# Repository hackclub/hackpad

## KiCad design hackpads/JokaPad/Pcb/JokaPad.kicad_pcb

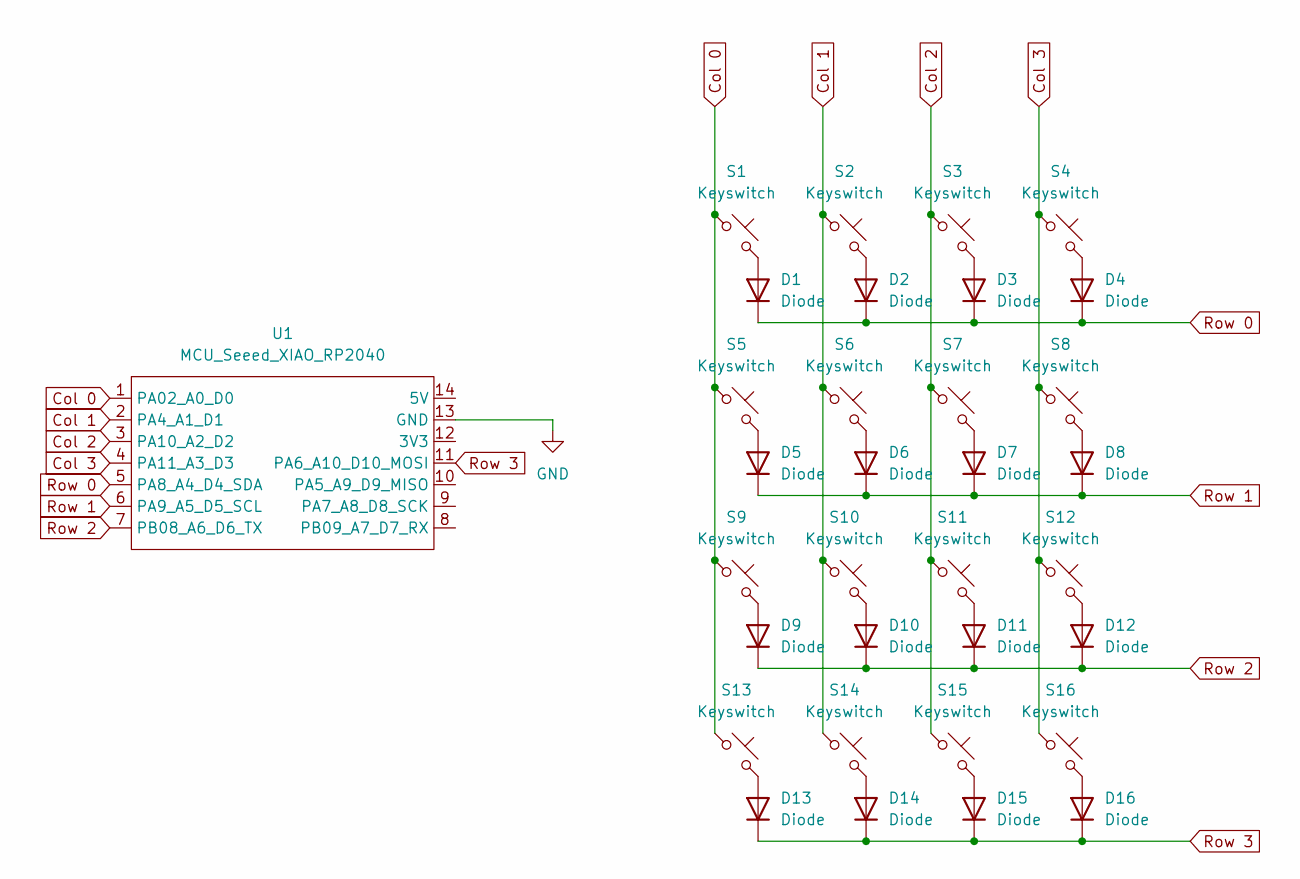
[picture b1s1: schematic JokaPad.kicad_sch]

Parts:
D1, D2, D3, D4, D5, D6, D7, D8, D9, D10, D11, D12, D13, D14, D15, D16: Diode; Diode_DO-35
S1, S2, S3, S4, S5, S6, S7, S8, S9, S10, S11, S12, S13, S14, S15, S16: Keyswitch; MX_PCB_1.00u
U1: MCU_Seeed_XIAO_RP2040; MOUDLE14P-2.54-21X17.8MM

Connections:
Col 0: S1.1, S5.1, S9.1, S13.1, U1.1 (PA02_A0_D0)
Col 1: S2.1, S6.1, S10.1, S14.1, U1.2 (PA4_A1_D1)
Col 2: S3.1, S7.1, S11.1, S15.1, U1.3 (PA10_A2_D2)
Col 3: S4.1, S8.1, S12.1, S16.1, U1.4 (PA11_A3_D3)
GND: U1.13 (GND)
unnamed: D1.2 (A), S1.2
unnamed: D2.2 (A), S2.2
unnamed: D3.2 (A), S3.2
unnamed: D4.2 (A), S4.2
unnamed: D5.2 (A), S5.2
unnamed: D6.2 (A), S6.2
unnamed: D7.2 (A), S7.2
unnamed: D8.2 (A), S8.2
unnamed: D9.2 (A), S9.2
unnamed: D10.2 (A), S10.2
unnamed: D11.2 (A), S11.2
unnamed: D12.2 (A), S12.2
unnamed: D13.2 (A), S13.2
unnamed: D14.2 (A), S14.2
unnamed: D15.2 (A), S15.2
unnamed: D16.2 (A), S16.2
Row 0: D1.1 (K), D2.1 (K), D3.1 (K), D4.1 (K), U1.5 (PA8_A4_D4_SDA)
Row 1: D5.1 (K), D6.1 (K), D7.1 (K), D8.1 (K), U1.6 (PA9_A5_D5_SCL)
Row 2: D9.1 (K), D10.1 (K), D11.1 (K), D12.1 (K), U1.7 (PB08_A6_D6_TX)
Row 3: D13.1 (K), D14.1 (K), D15.1 (K), D16.1 (K), U1.11 (PA6_A10_D10_MOSI)

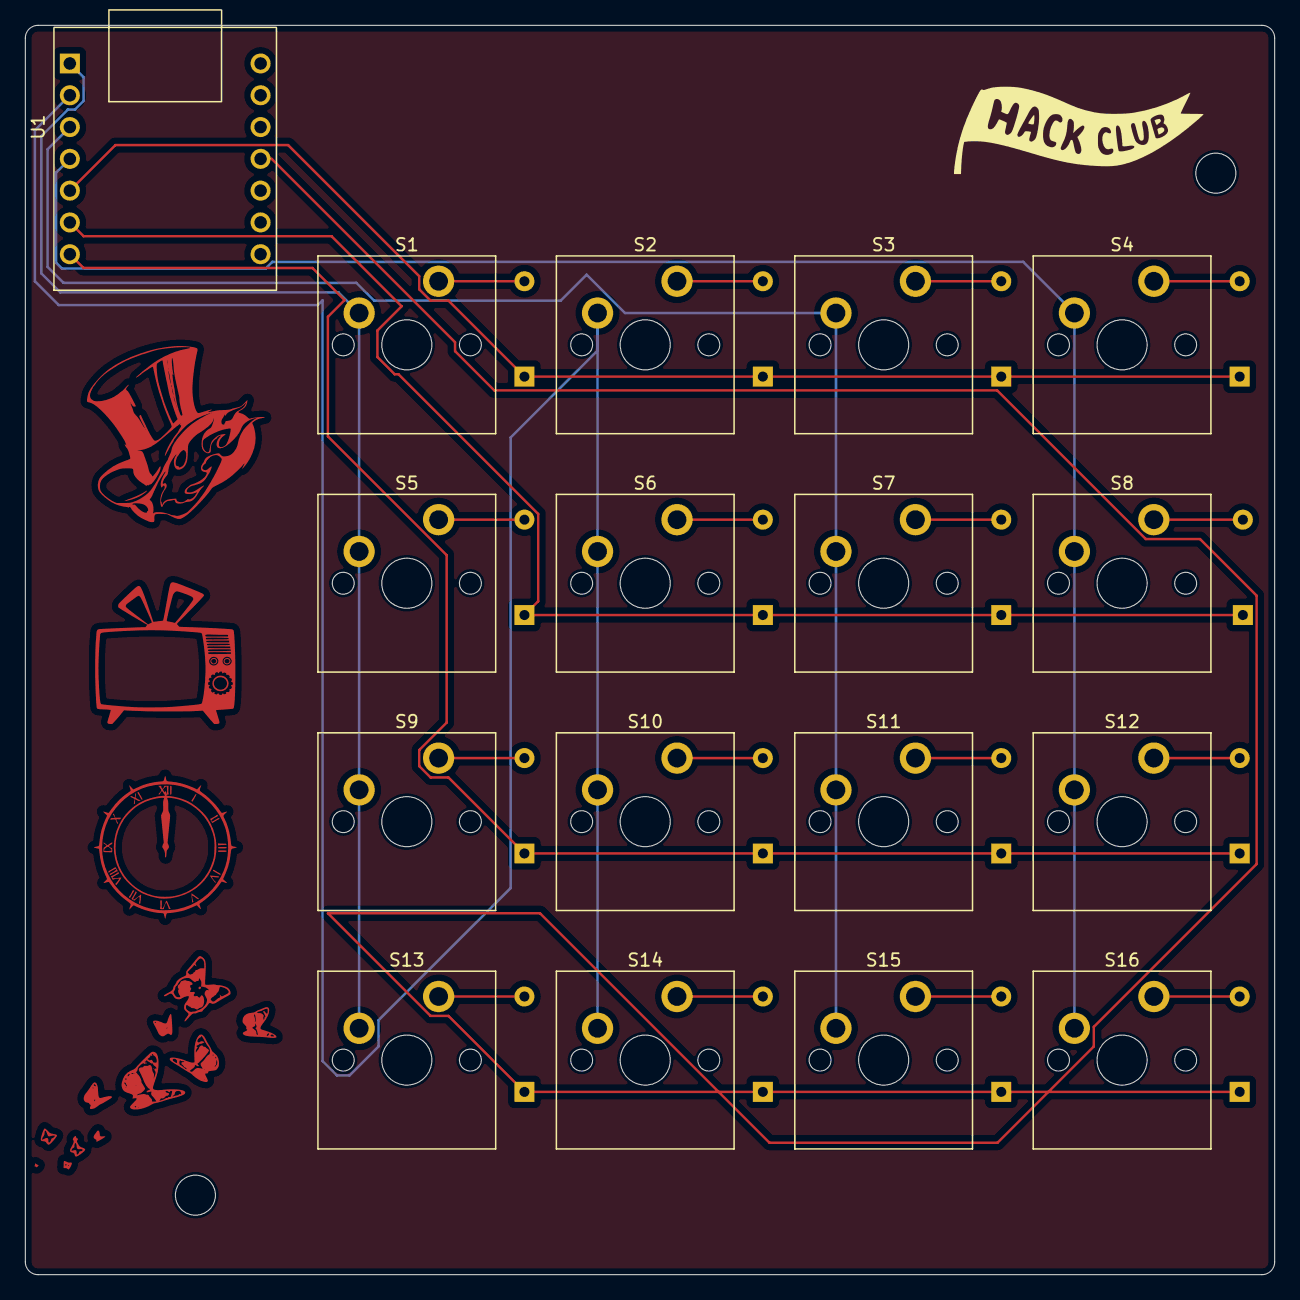
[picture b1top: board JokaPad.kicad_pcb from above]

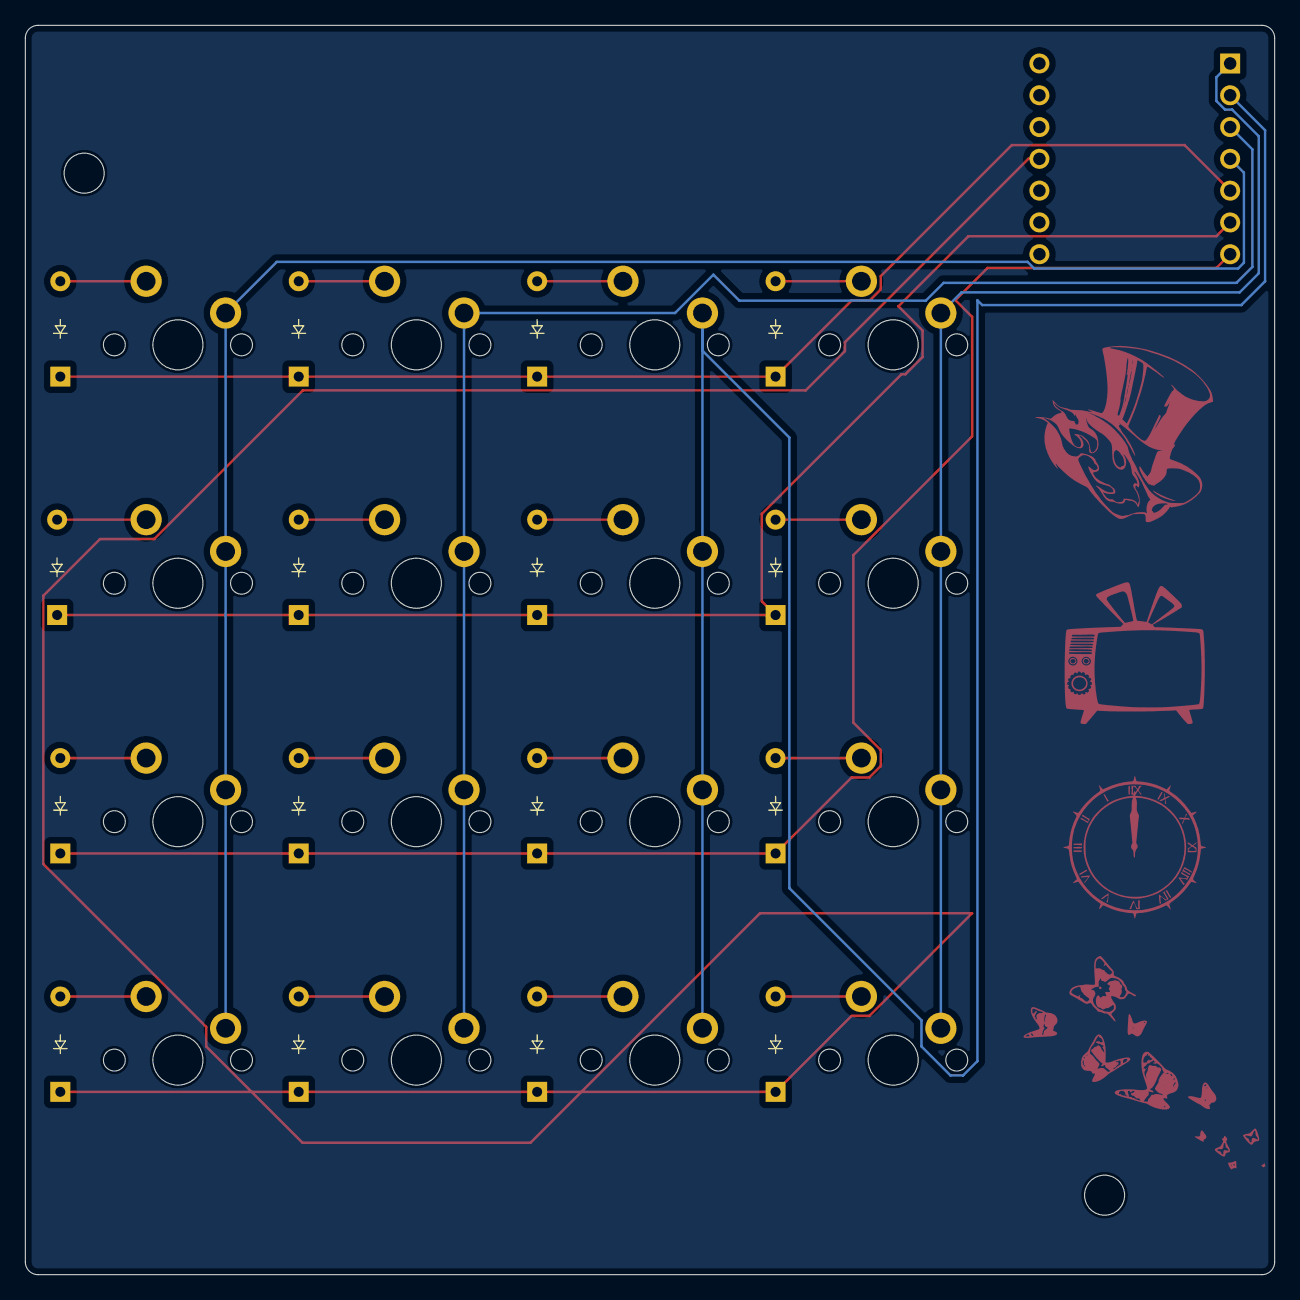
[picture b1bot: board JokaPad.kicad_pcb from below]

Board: 2 copper layers, 99.8 x 99.8 mm, 33 parts (16 on the bottom side), 24 nets.

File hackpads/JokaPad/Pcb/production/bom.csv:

Designator,Footprint,Quantity,Value,LCSC Part #
"D1, D10, D11, D12, D13, D14, D15, D16, D2, D3, D4, D5, D6, D7, D8, D9",Diode_DO-35,16,Diode,
"S1, S10, S11, S12, S13, S14, S15, S16, S2, S3, S4, S5, S6, S7, S8, S9",MX_PCB_1.00u,16,Keyswitch,
U1,MOUDLE14P-2.54-21X17.8MM,1,MCU_Seeed_XIAO_RP2040,

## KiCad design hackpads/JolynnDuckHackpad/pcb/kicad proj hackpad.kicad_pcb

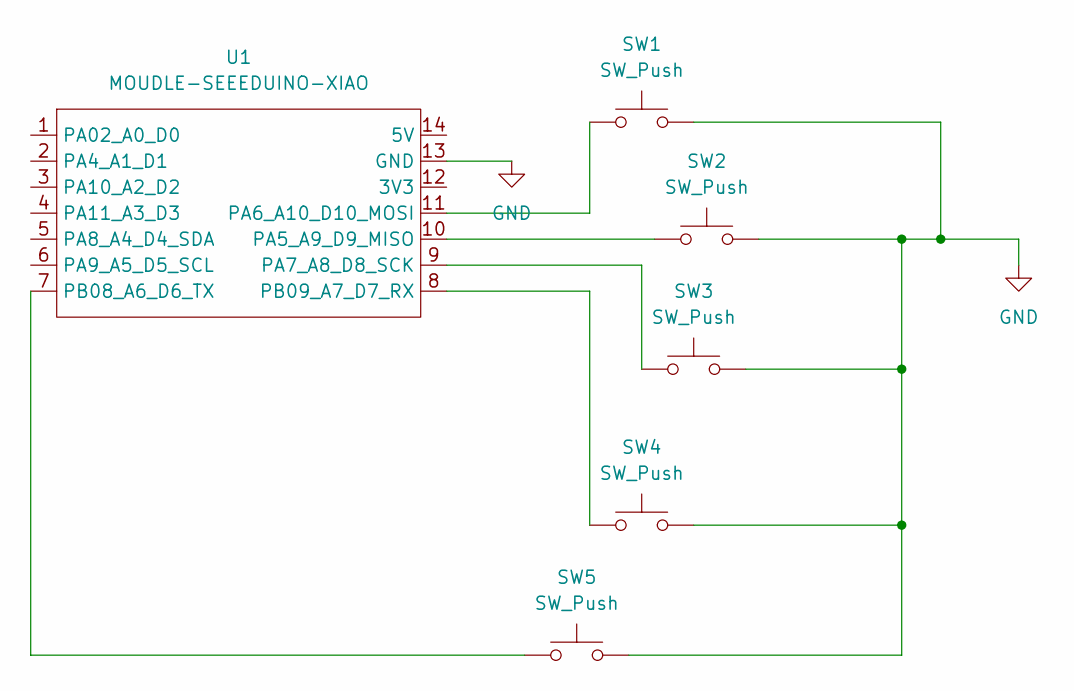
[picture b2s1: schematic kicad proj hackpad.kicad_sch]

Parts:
SW1, SW2, SW3, SW4, SW5: SW_Push; SW_Cherry_MX_1.00u_PCB
U1: MOUDLE-SEEEDUINO-XIAO; XIAO-Generic-Hybrid-14P-2.54-21X17.8MM

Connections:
GND: SW1.2, SW2.2, SW3.2, SW4.2, SW5.2, U1.13 (GND)
unnamed: SW2.1, U1.10 (PA5_A9_D9_MISO)
unnamed: SW1.1, U1.11 (PA6_A10_D10_MOSI)
unnamed: SW3.1, U1.9 (PA7_A8_D8_SCK)
unnamed: SW5.1, U1.7 (PB08_A6_D6_TX)
unnamed: SW4.1, U1.8 (PB09_A7_D7_RX)

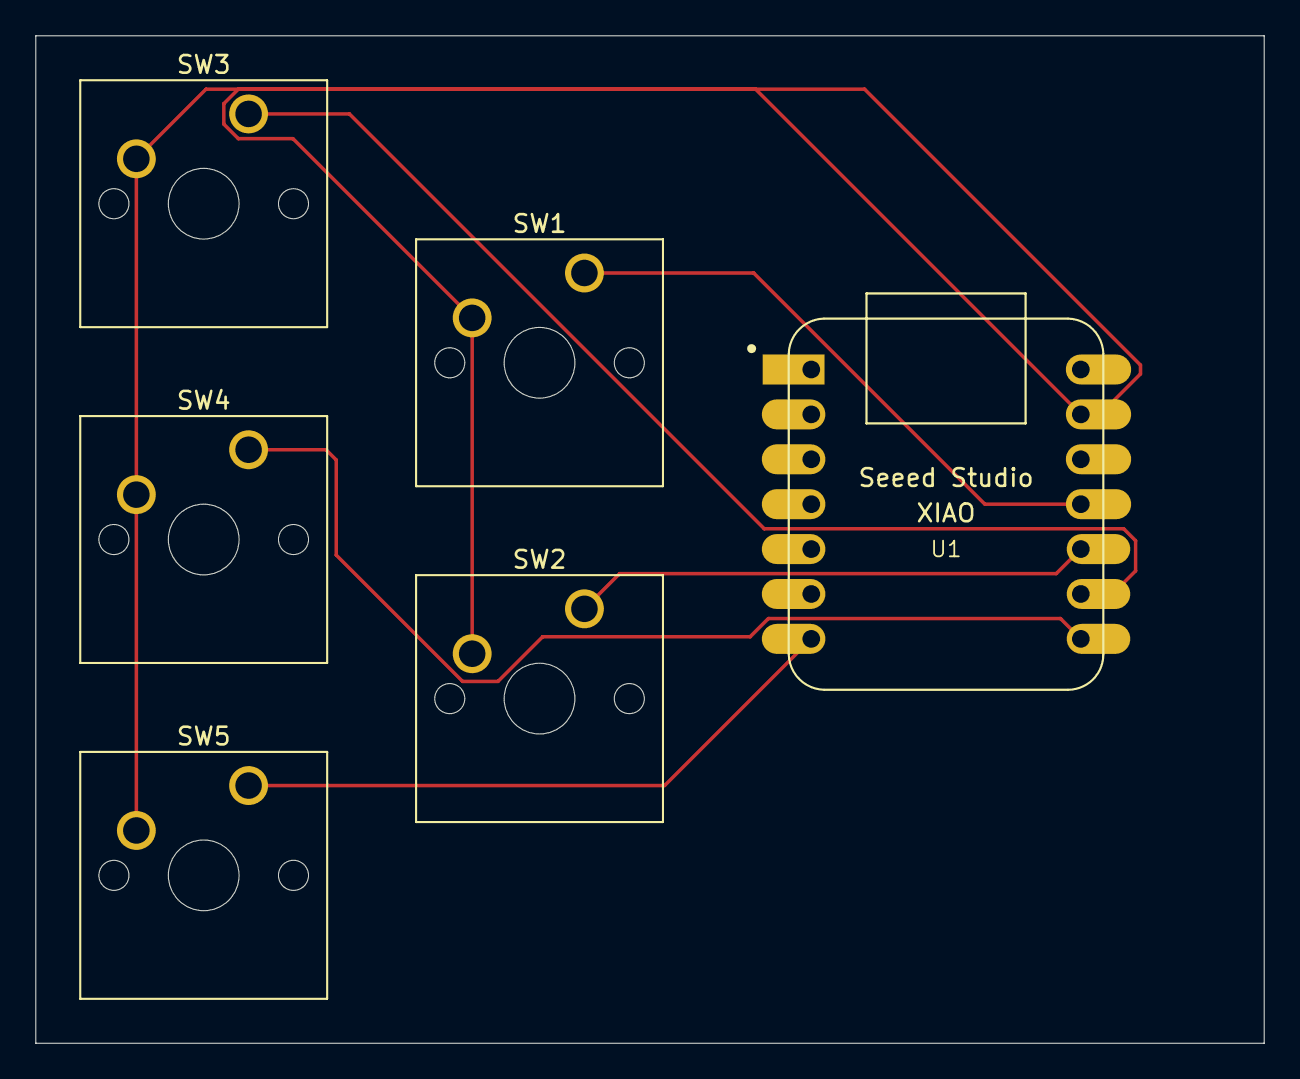
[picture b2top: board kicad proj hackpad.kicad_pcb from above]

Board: 2 copper layers, 69.5 x 57.0 mm, 6 parts (0 on the bottom side), 6 nets.

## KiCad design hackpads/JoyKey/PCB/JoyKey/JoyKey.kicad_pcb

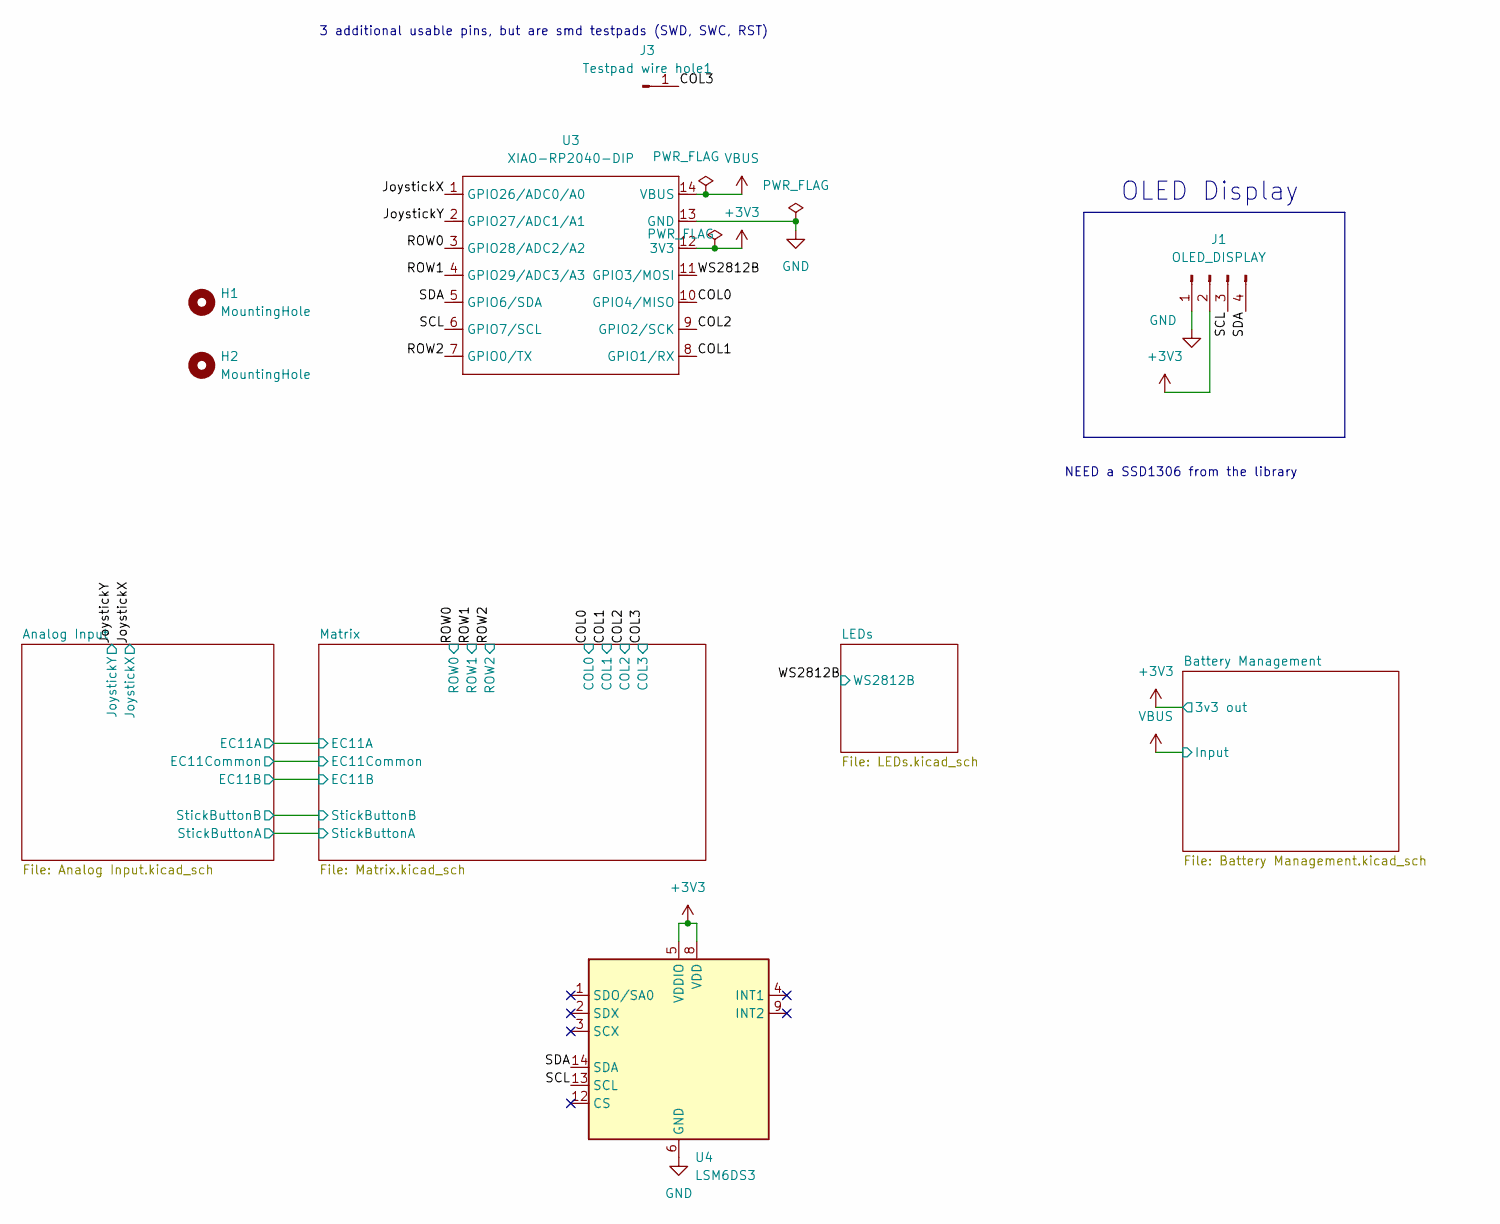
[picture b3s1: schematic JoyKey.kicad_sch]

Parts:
H1, H2: MountingHole; MountingHole_3.2mm_M3_Pad
J1: OLED_DISPLAY; SSD1306-OLED096-128x64
J3: Testpad wire hole1; PinHeader_1x01_P2.54mm_Vertical
U3: XIAO-RP2040-DIP
U4: LSM6DS3; LGA-14_3x2.5mm_P0.5mm_LayoutBorder3x4y_COSTSAVERPADs

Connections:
+3V3: J1.2, U3.12 (3V3), U4.5 (VDDIO), U4.8 (VDD); also elsewhere on the board
/COL0: U3.10 (GPIO4/MISO); also elsewhere on the board
/COL1: U3.8 (GPIO1/RX); also elsewhere on the board
/COL2: U3.9 (GPIO2/SCK); also elsewhere on the board
/COL3: J3.1; also elsewhere on the board
/JoystickX: U3.1 (GPIO26/ADC0/A0); also elsewhere on the board
/JoystickY: U3.2 (GPIO27/ADC1/A1); also elsewhere on the board
/ROW0: U3.3 (GPIO28/ADC2/A2); also elsewhere on the board
/ROW1: U3.4 (GPIO29/ADC3/A3); also elsewhere on the board
/ROW2: U3.7 (GPIO0/TX); also elsewhere on the board
/SCL: J1.3, U3.6 (GPIO7/SCL), U4.13 (SCL)
/SDA: J1.4, U3.5 (GPIO6/SDA), U4.14 (SDA)
/WS2812B: U3.11 (GPIO3/MOSI); also elsewhere on the board
GND: J1.1, U3.13 (GND), U4.6 (GND), U4.7 (GND); also elsewhere on the board
VBUS: U3.14 (VBUS); also elsewhere on the board

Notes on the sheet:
NEED a SSD1306 from the library
OLED Display
3 additional usable pins, but are smd testpads (SWD, SWC, RST)

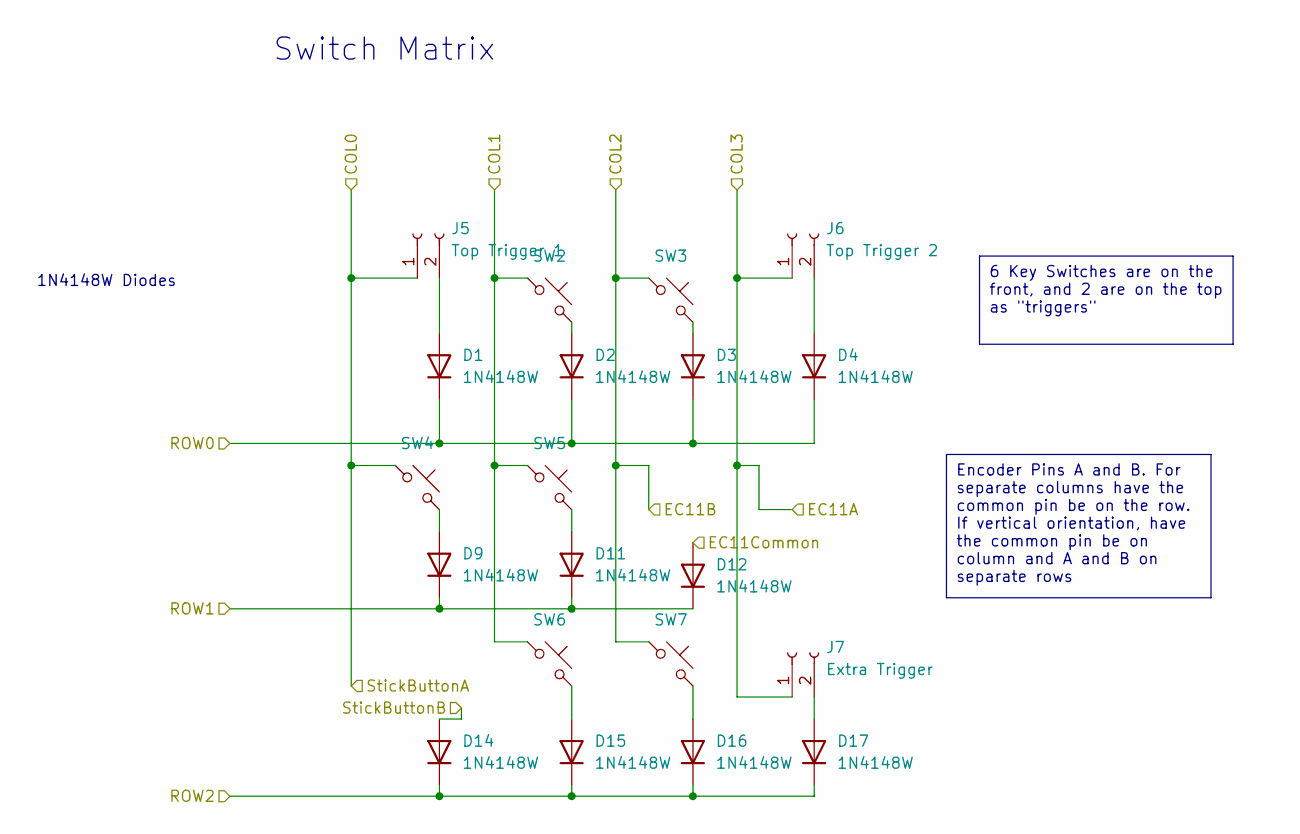
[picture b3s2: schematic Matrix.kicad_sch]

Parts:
D1, D2, D3, D4, D9, D11, D12, D14, D15, D16, D17: 1N4148W; Nexperia_CFP3_SOD-123W
J5: Top Trigger 1; PinHeader_1x02_P2.54mm_Vertical
J6: Top Trigger 2; PinHeader_1x02_P2.54mm_Vertical
J7: Extra Trigger; PinHeader_1x02_P2.54mm_Vertical
SW2, SW3, SW4, SW5, SW6, SW7: SW_Push_45deg; MX-Solderable-1U

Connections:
/Analog Input/EC11Common: D12.2 (A); also elsewhere on the board
/Analog Input/StickButtonB: D14.2 (A); also elsewhere on the board
/COL0: J5.1, SW4.1; also elsewhere on the board
/COL1: SW2.1, SW5.1, SW6.1; also elsewhere on the board
/COL2: SW3.1, SW7.1; also elsewhere on the board
/COL3: J6.1, J7.1; also elsewhere on the board
/ROW0: D1.1 (K), D2.1 (K), D3.1 (K), D4.1 (K); also elsewhere on the board
/ROW1: D9.1 (K), D11.1 (K), D12.1 (K); also elsewhere on the board
/ROW2: D14.1 (K), D15.1 (K), D16.1 (K), D17.1 (K); also elsewhere on the board
unnamed: D1.2 (A), J5.2
unnamed: D2.2 (A), SW2.2
unnamed: D3.2 (A), SW3.2
unnamed: D4.2 (A), J6.2
unnamed: D9.2 (A), SW4.2
unnamed: D11.2 (A), SW5.2
unnamed: D15.2 (A), SW6.2
unnamed: D16.2 (A), SW7.2
unnamed: D17.2 (A), J7.2

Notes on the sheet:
Encoder Pins A and B. For separate columns have the common pin be on the row. If vertical orientation, have the common pin be on column and A and B on separate rows
6 Key Switches are on the front, and 2 are on the top as "triggers"
Switch Matrix
1N4148W Diodes

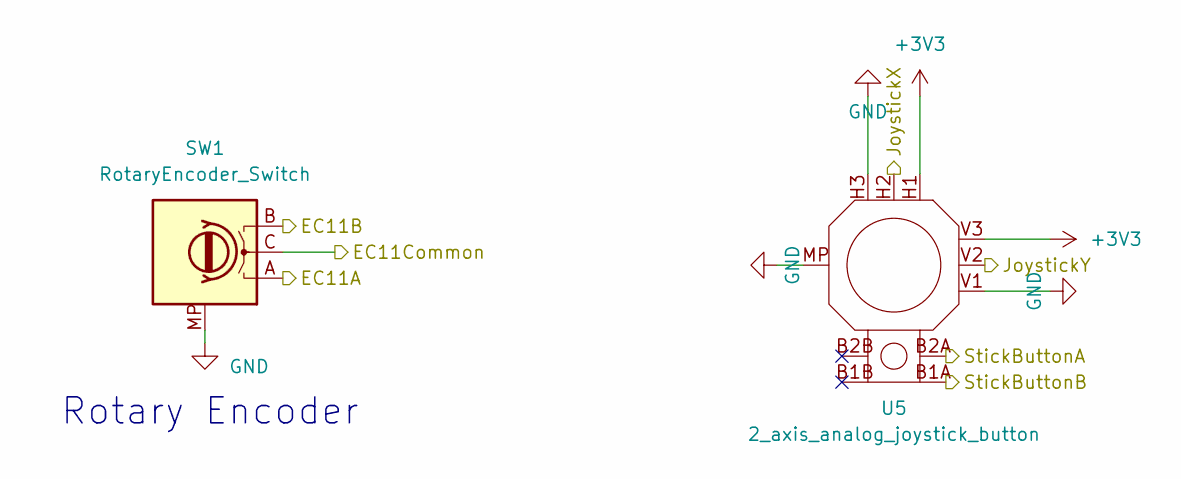
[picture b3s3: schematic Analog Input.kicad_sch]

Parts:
SW1: RotaryEncoder_Switch; RotaryEncoder_Alps_EC12E_Vertical_H20mm
U5: 2_axis_analog_joystick_button; Adafruit 2-Axis joystick

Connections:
+3V3: U5.H1, U5.V3; also elsewhere on the board
/Analog Input/EC11Common: SW1.C; also elsewhere on the board
/Analog Input/StickButtonB: U5.B1A; also elsewhere on the board
/COL0: U5.B2A; also elsewhere on the board
/COL2: SW1.B; also elsewhere on the board
/COL3: SW1.A; also elsewhere on the board
/JoystickX: U5.H2; also elsewhere on the board
/JoystickY: U5.V2; also elsewhere on the board
GND: SW1.MP, U5.H3, U5.MP, U5.V1; also elsewhere on the board

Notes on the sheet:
Rotary Encoder

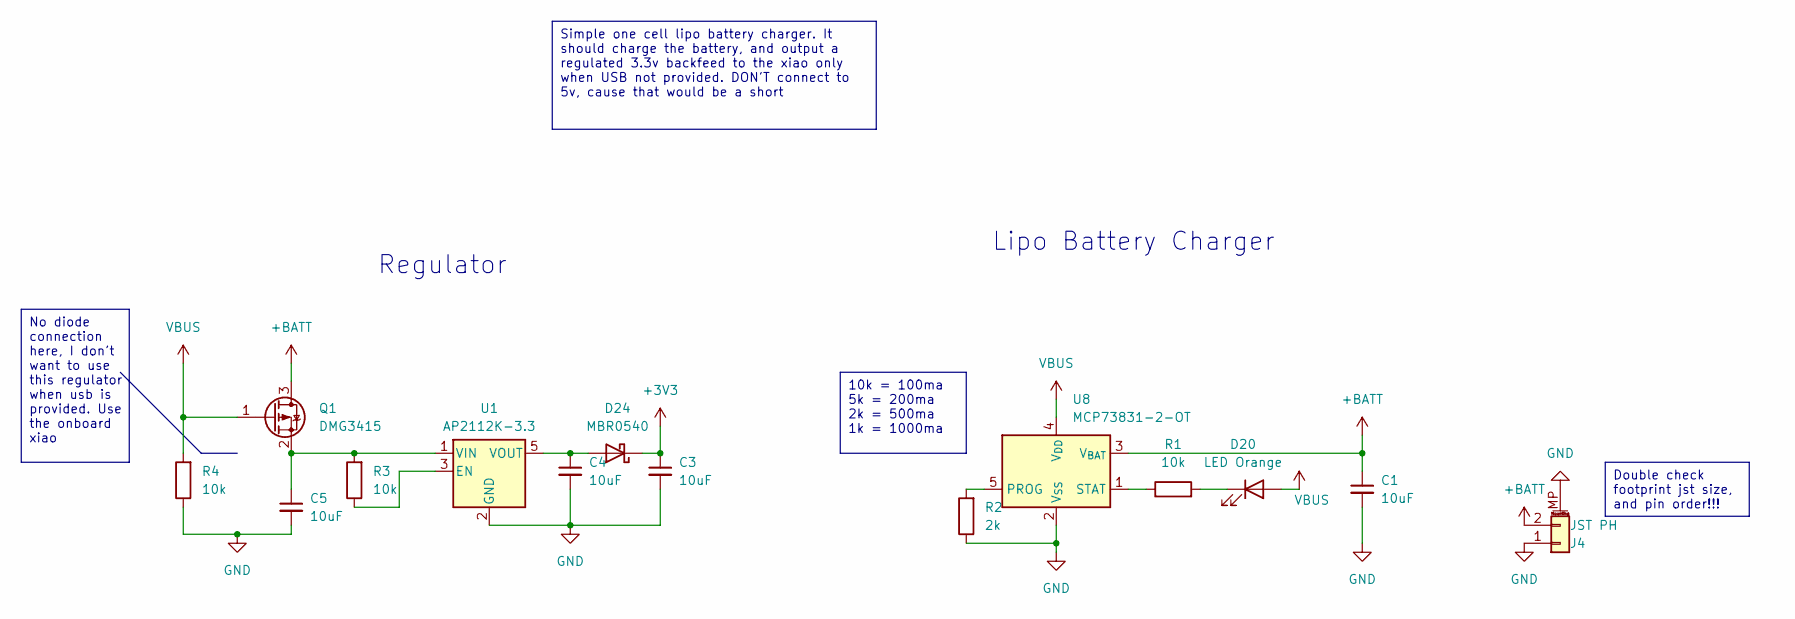
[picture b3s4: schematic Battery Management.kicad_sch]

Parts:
C1, C3, C4, C5: 10uF; C_0805_2012Metric
D20: LED Orange; LED_0603_1608Metric
D24: MBR0540; Nexperia_CFP3_SOD-123W
J4: JST PH; JST_PH_S2B-PH-SM4-TB_1x02-1MP_P2.00mm_Horizontal
Q1: DMG3415; SOT-23-3
R1, R3, R4: 10k; R_0805_2012Metric
R2: 2k; R_0805_2012Metric
U1: AP2112K-3.3; SOT-23-5
U8: MCP73831-2-OT; SOT-23-5

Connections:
+3V3: C3.1, D24.1 (K); also elsewhere on the board
+BATT: C1.1, J4.2, Q1.3 (D), U8.3 (V_{BAT})
GND: C1.2, C3.2, C4.2, C5.2, J4.1, J4.MP (MountPin), R2.1, R4.1, U1.2 (GND), U8.2 (V_{SS}); also elsewhere on the board
unnamed: D20.1 (K), R1.2
unnamed: C4.1, D24.2 (A), U1.5 (VOUT)
unnamed: C5.1, Q1.2 (S), R3.2, U1.1 (VIN)
unnamed: R3.1, U1.3 (EN)
unnamed: R2.2, U8.5 (PROG)
unnamed: R1.1, U8.1 (STAT)
VBUS: D20.2 (A), Q1.1 (G), R4.2, U8.4 (V_{DD}); also elsewhere on the board

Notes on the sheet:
10k = 100ma 5k = 200ma 2k = 500ma 1k = 1000ma
No diode connection here, I don't want to use this regulator when usb is provided. Use the onboard xiao
Simple one cell lipo battery charger. It should charge the battery, and output a regulated 3.3v backfeed to the xiao only when USB not provided. DON'T connect to 5v, cause that would be a short
Double check footprint jst size, and pin order!!!
Lipo Battery Charger
Regulator

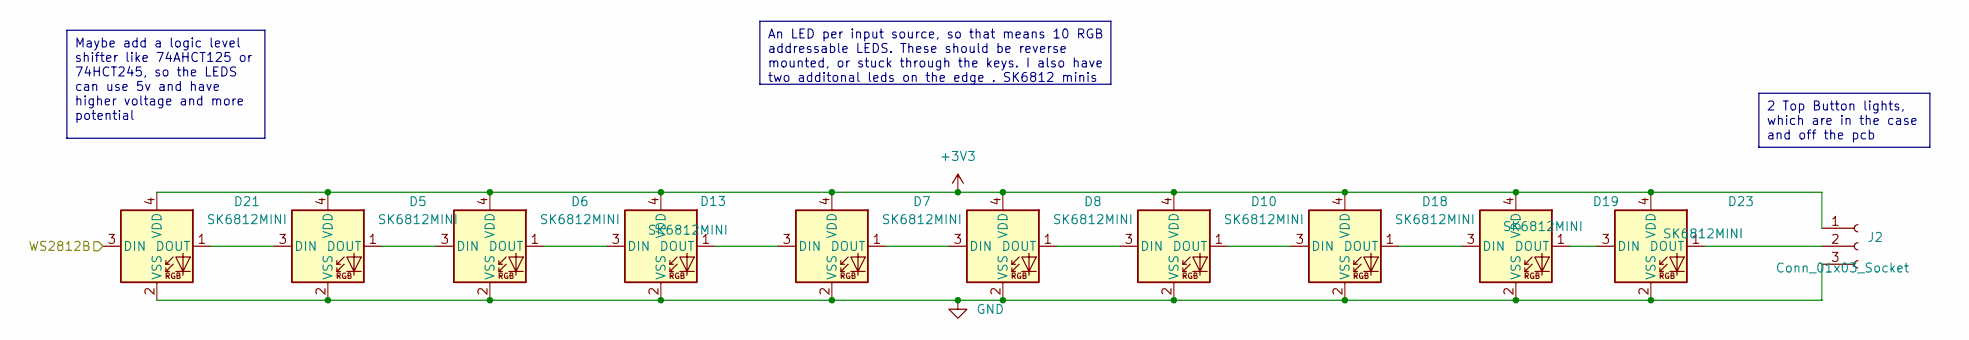
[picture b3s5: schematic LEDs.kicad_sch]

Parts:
D5, D6, D7, D8, D10, D13, D18, D19, D21, D23: SK6812MINI; SK6812MINI-E
J2: Conn_01x03_Socket; PinHeader_1x03_P2.54mm_Vertical

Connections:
+3V3: D5.4 (VDD), D6.4 (VDD), D7.4 (VDD), D8.4 (VDD), D10.4 (VDD), D13.4 (VDD), D18.4 (VDD), D19.4 (VDD), D21.4 (VDD), D23.4 (VDD), J2.1; also elsewhere on the board
/WS2812B: D21.3 (DIN); also elsewhere on the board
GND: D5.2 (VSS), D6.2 (VSS), D7.2 (VSS), D8.2 (VSS), D10.2 (VSS), D13.2 (VSS), D18.2 (VSS), D19.2 (VSS), D21.2 (VSS), D23.2 (VSS), J2.3; also elsewhere on the board
unnamed: D5.1 (DOUT), D6.3 (DIN)
unnamed: D7.1 (DOUT), D8.3 (DIN)
unnamed: D8.1 (DOUT), D10.3 (DIN)
unnamed: D10.1 (DOUT), D18.3 (DIN)
unnamed: D6.1 (DOUT), D13.3 (DIN)
unnamed: D7.3 (DIN), D13.1 (DOUT)
unnamed: D18.1 (DOUT), D19.3 (DIN)
unnamed: D19.1 (DOUT), D23.3 (DIN)
unnamed: D5.3 (DIN), D21.1 (DOUT)
unnamed: D23.1 (DOUT), J2.2

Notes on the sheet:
2 Top Button lights, which are in the case and off the pcb
An LED per input source, so that means 10 RGB addressable LEDS. These should be reverse mounted, or stuck through the keys. I also have two additonal leds on the edge . SK6812 minis
Maybe add a logic level shifter like 74AHCT125 or 74HCT245, so the LEDS can use 5v and have higher voltage and more potential

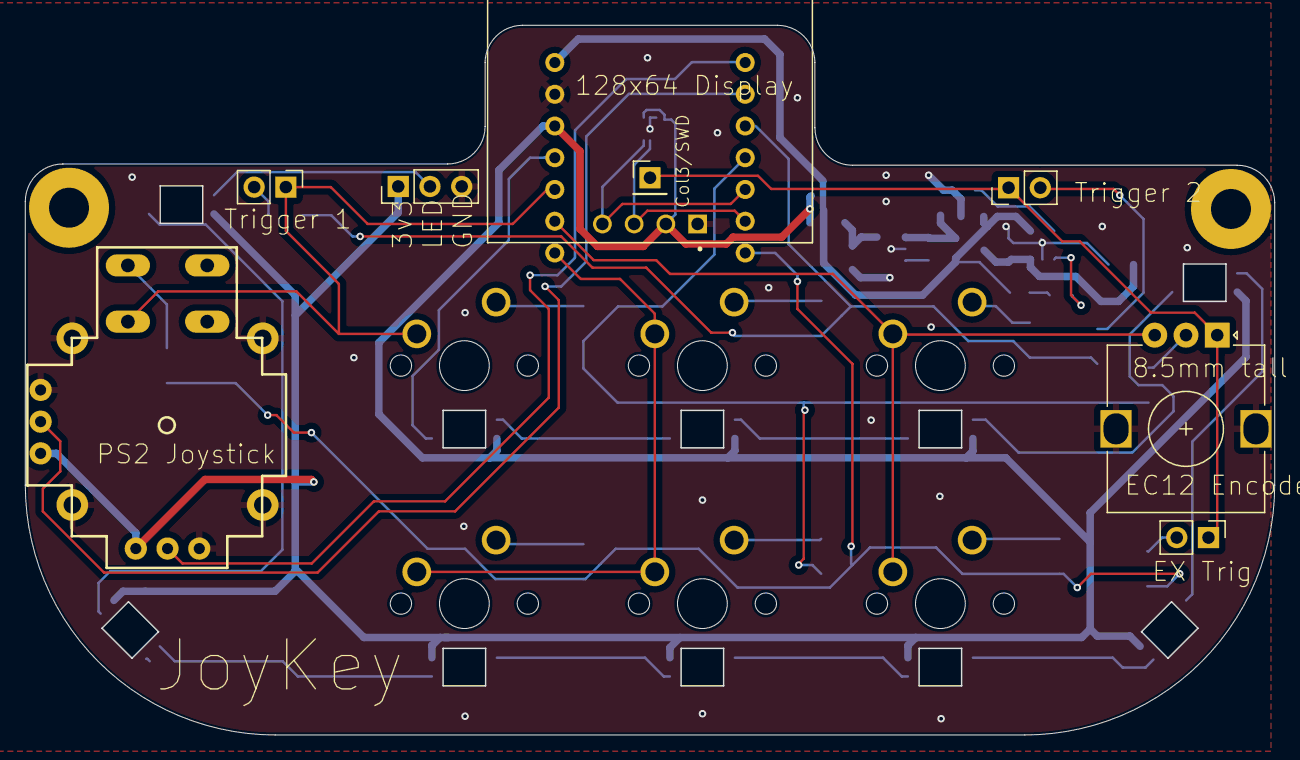
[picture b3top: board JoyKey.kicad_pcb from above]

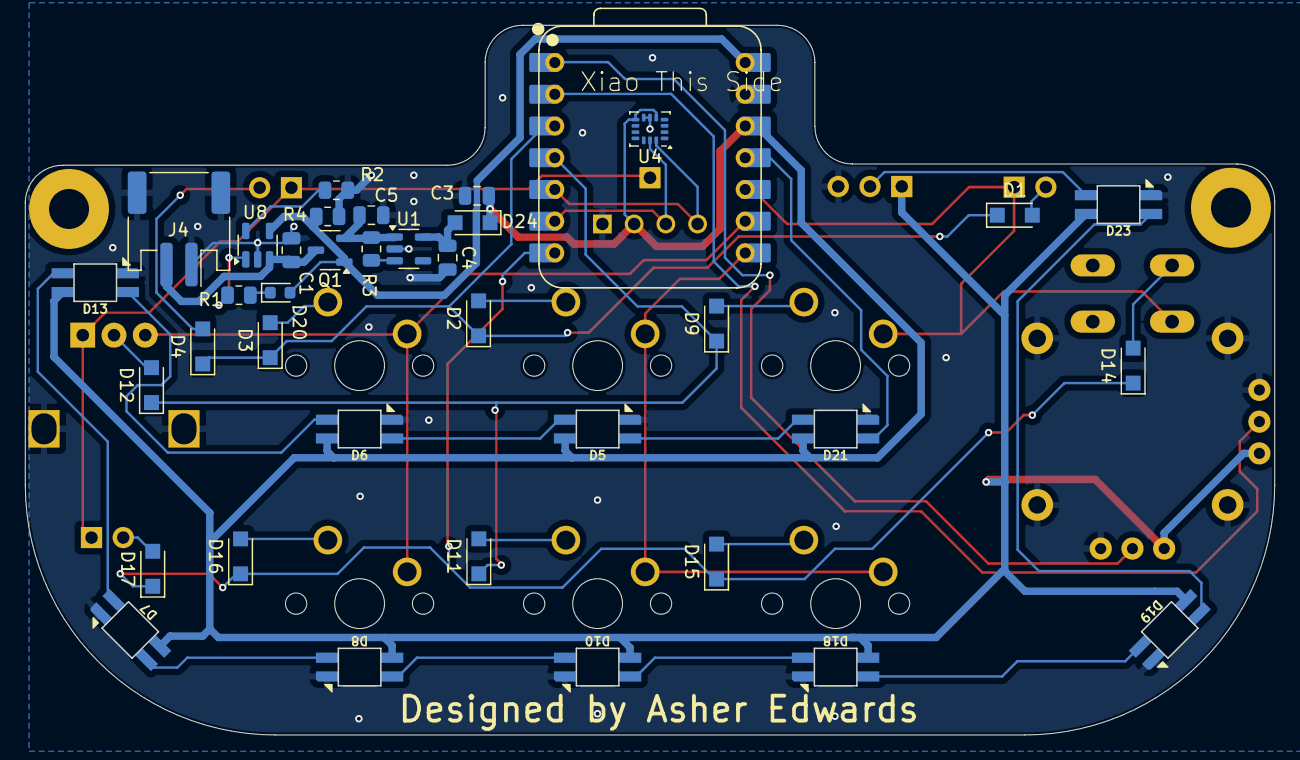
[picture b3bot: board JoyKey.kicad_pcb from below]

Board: 2 copper layers, 100.0 x 56.8 mm, 53 parts (37 on the bottom side), 43 nets.

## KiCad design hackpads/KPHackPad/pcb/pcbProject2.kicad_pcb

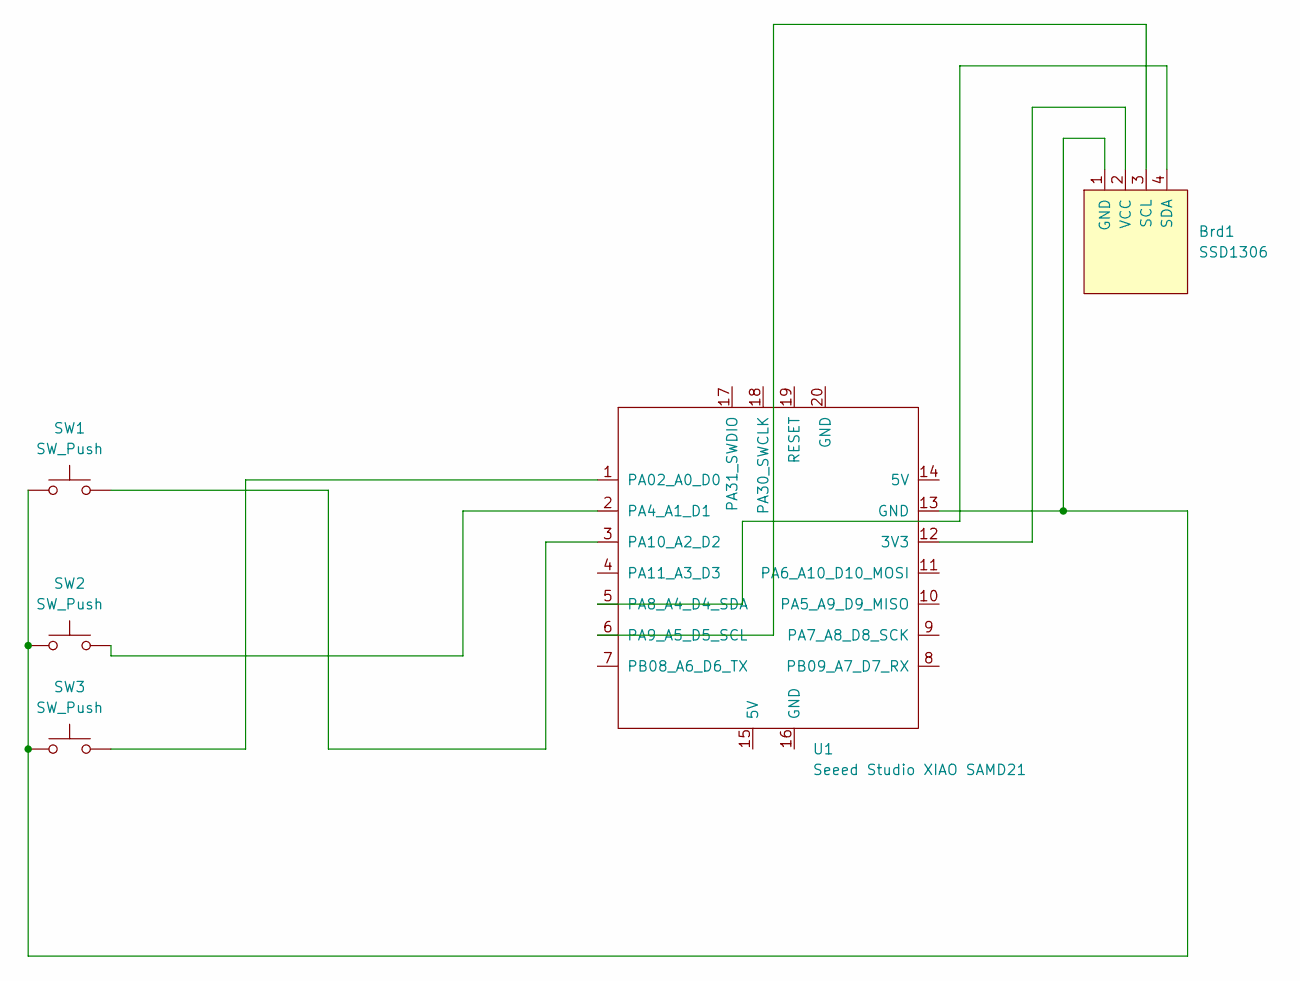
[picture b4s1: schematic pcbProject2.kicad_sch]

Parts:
Brd1: SSD1306; 128x64OLED
SW1, SW2, SW3: SW_Push; SW_Cherry_MX_1.00u_PCB
U1: Seeed Studio XIAO SAMD21; XIAO-Generic-Thruhole-14P-2.54-21X17.8MM

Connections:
unnamed: Brd1.1 (GND), SW1.1, SW2.1, SW3.1, U1.13 (GND)
unnamed: Brd1.3 (SCL), U1.6 (PA9_A5_D5_SCL)
unnamed: Brd1.4 (SDA), U1.5 (PA8_A4_D4_SDA)
unnamed: Brd1.2 (VCC), U1.12 (3V3)
unnamed: SW3.2, U1.1 (PA02_A0_D0)
unnamed: SW2.2, U1.2 (PA4_A1_D1)
unnamed: SW1.2, U1.3 (PA10_A2_D2)

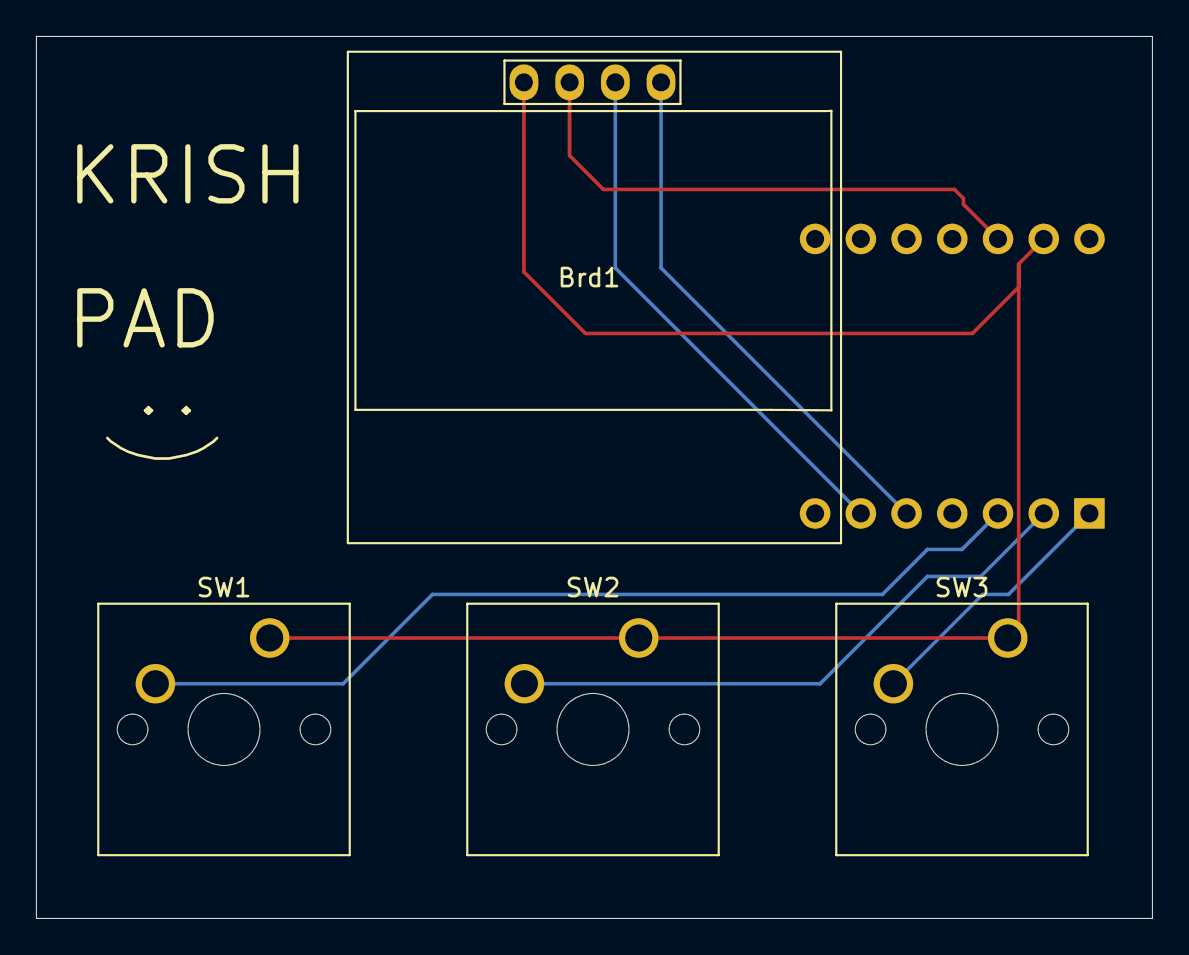
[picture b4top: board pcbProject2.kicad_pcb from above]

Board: 2 copper layers, 62.0 x 49.0 mm, 5 parts (1 on the bottom side), 7 nets.
